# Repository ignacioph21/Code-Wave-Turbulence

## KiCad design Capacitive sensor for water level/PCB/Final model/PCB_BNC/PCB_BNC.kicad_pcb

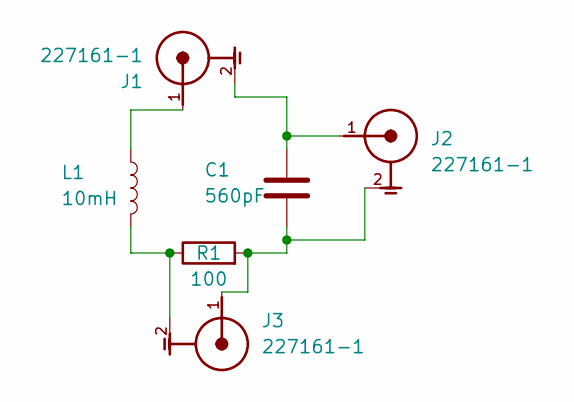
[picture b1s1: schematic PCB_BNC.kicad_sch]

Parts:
C1: 560pF; C_Disc_D12.5mm_W5.0mm_P7.50mm
J1, J2, J3: 227161-1; TE_227161-1; VOLTAGE_RATING_AC 500V; PART_DESCRIPTION CONN BNC JACK R/A 50 OHM PCB
L1: 10mH; L_Axial_L5.3mm_D2.2mm_P10.16mm_Horizontal_Vishay_IM-1
R1: 100; R_Axial_DIN0207_L6.3mm_D2.5mm_P7.62mm_Horizontal

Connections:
unnamed: C1.1, J2.2, J3.1, R1.2
unnamed: C1.2, J1.2, J2.1
unnamed: J1.1, L1.1
unnamed: J3.2, L1.2, R1.1

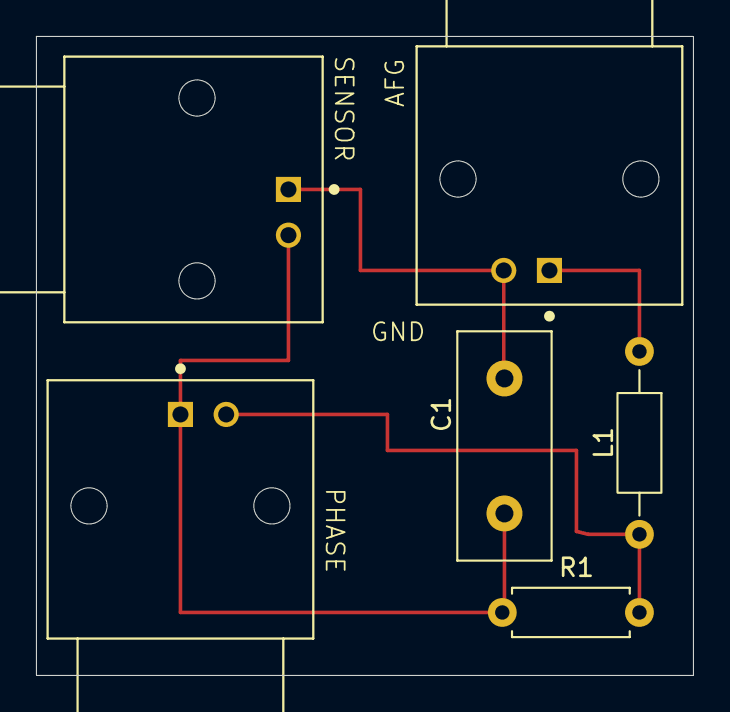
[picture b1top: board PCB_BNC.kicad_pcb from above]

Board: 2 copper layers, 36.5 x 35.5 mm, 6 parts (0 on the bottom side), 4 nets.

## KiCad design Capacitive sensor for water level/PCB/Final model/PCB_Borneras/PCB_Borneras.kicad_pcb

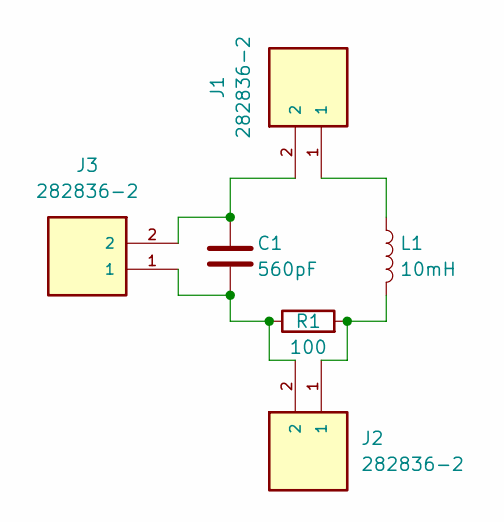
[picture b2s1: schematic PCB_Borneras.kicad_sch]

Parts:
C1: 560pF; C_Disc_D12.5mm_W5.0mm_P7.50mm
J1, J2, J3: 282836-2; TE_282836-2; PARTREV J1
L1: 10mH; L_Axial_L5.3mm_D2.2mm_P10.16mm_Horizontal_Vishay_IM-1
R1: 100; R_Axial_DIN0207_L6.3mm_D2.5mm_P7.62mm_Horizontal

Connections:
unnamed: C1.1, J2.2, J3.1, R1.1
unnamed: C1.2, J1.2, J3.2
unnamed: J1.1, L1.1
unnamed: J2.1, L1.2, R1.2

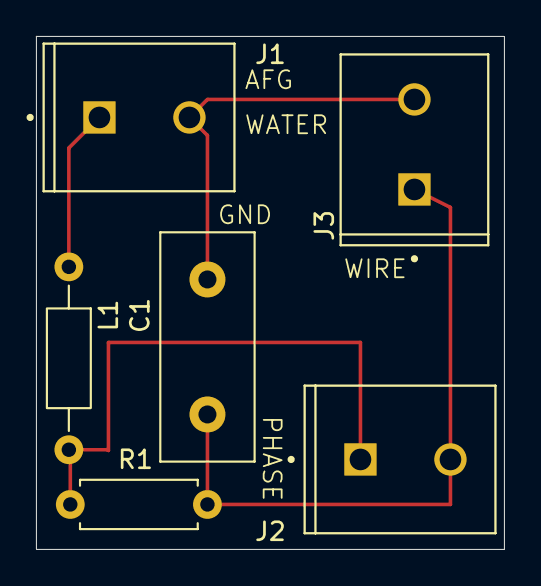
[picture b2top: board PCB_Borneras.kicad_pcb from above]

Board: 2 copper layers, 26.0 x 28.5 mm, 6 parts (0 on the bottom side), 4 nets.

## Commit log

2025-04-06 Updates to README.md
2025-04-09 Simulation of the sensor.
2025-04-09 First prototype for the sensor cover.
2025-06-02 PCB design for the sensor.
2025-06-02 Corrected filesa.
2025-06-17 Add software for DAQ control and lockin for the sensor.
2025-06-18 Improved code for the DAQ.
2025-06-18 All necessary files for a measurement.
2025-06-20 Multiple modes for lock_in configurations.
